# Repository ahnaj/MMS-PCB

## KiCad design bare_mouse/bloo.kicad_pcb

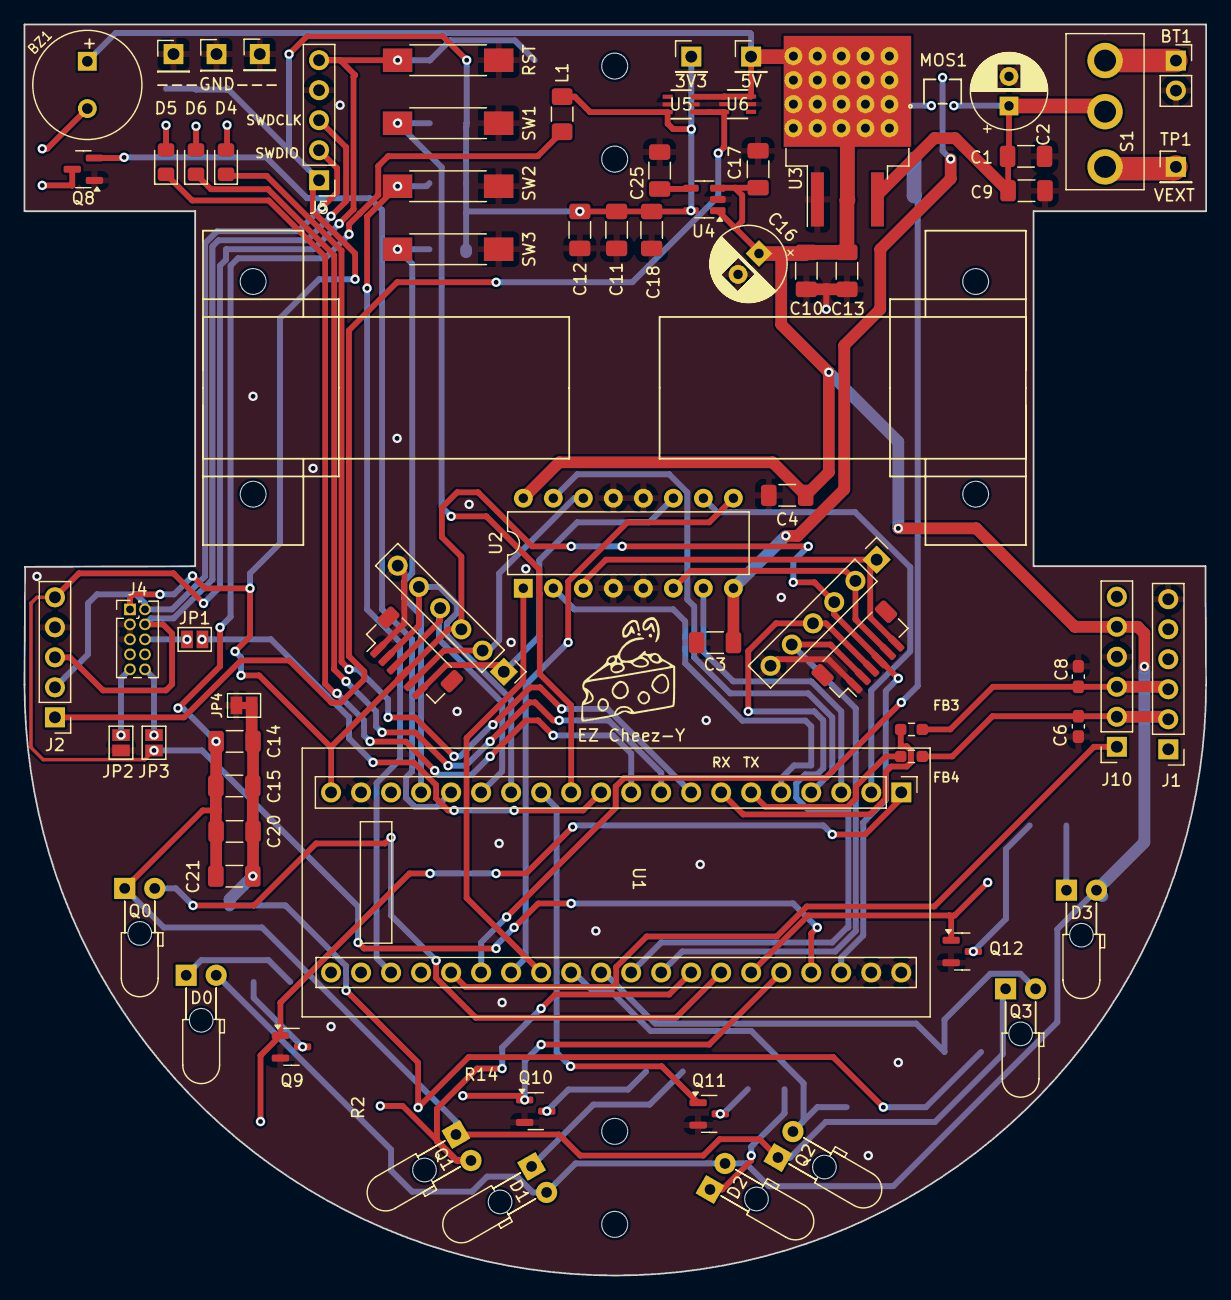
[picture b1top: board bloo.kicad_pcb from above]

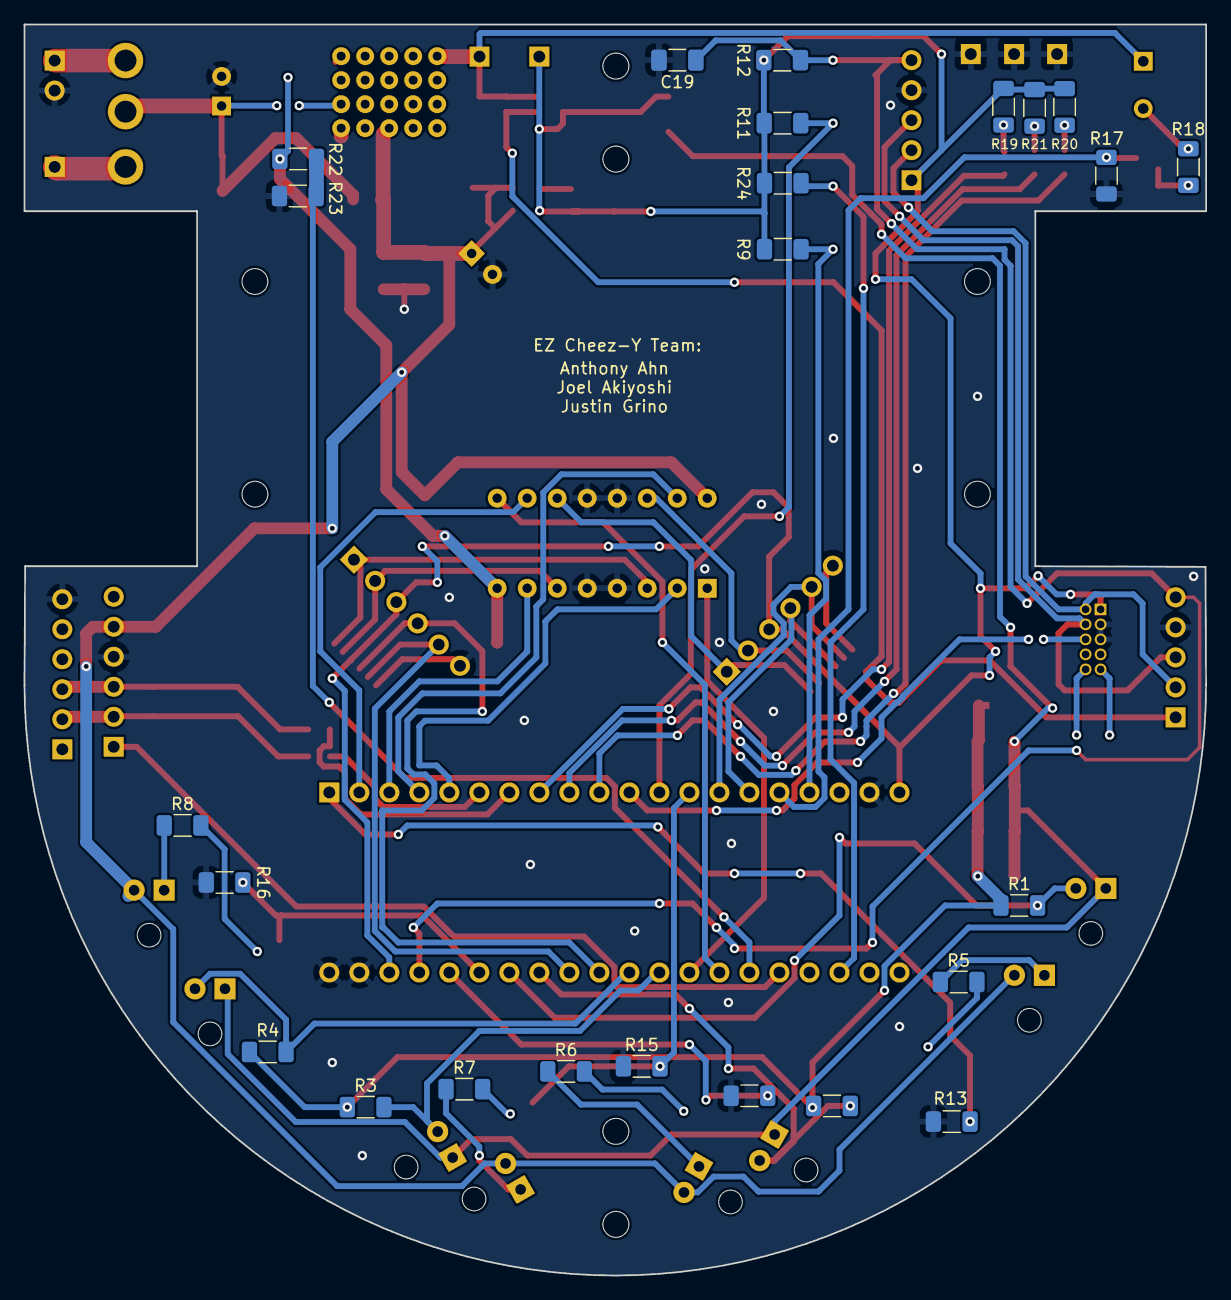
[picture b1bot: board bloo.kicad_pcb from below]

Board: 2 copper layers, 100.0 x 105.9 mm, 99 parts (24 on the bottom side), 66 nets.

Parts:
BT1: Battery_Cell; PinSocket_1x02_P2.54mm_Vertical
BZ1: Buzzer; MagneticBuzzer_PUI_AT-0927-TT-6-R
C1, C4, C12, C13, C19: 0.1uF; C_1206_3216Metric_Pad1.33x1.80mm_HandSolder
C2, C16: 100uF; CP_Radial_D6.3mm_P2.50mm
C3, C14, C15, C17, C18, C20, C21: 1uF; C_1206_3216Metric_Pad1.33x1.80mm_HandSolder
C6, C8: 22pF; C_0603_1608Metric_Pad1.08x0.95mm_HandSolder
C9, C11: 10uF; C_1206_3216Metric_Pad1.33x1.80mm_HandSolder
C10: 10uF(Tantalum); C_1206_3216Metric_Pad1.33x1.80mm_HandSolder
C25: 10nF; C_1206_3216Metric_Pad1.33x1.80mm_HandSolder
D0, D1, D2, D3: SFH4545; Emitter
D4, D5, D6: LED; LED_0805_2012Metric_Pad1.15x1.40mm_HandSolder
FB3, FB4: HZ0603C601R-10; R_0603_1608Metric_Pad0.98x0.95mm_HandSolder
J1: Serial Debug Header; PinHeader_1x06_P2.54mm_Vertical
J2, J5: SWD Header; PinHeader_1x05_P2.54mm_Vertical
J4: Conn_ARM_JTAG_SWD_10; PinHeader_2x05_P1.27mm_Vertical
J10: Conn_01x06_Female; PinSocket_1x06_P2.54mm_Vertical
JP1: JP_SWO; SolderJumper-2_P1.3mm_Open_Pad1.0x1.5mm
JP2: JP_GND; SolderJumper-2_P1.3mm_Open_Pad1.0x1.5mm
JP3: JP_RST; SolderJumper-2_P1.3mm_Open_Pad1.0x1.5mm
JP4: Jumper_2_Open; SolderJumper-2_P1.3mm_Bridged_Pad1.0x1.5mm
L1: 10uH; L_1206_3216Metric_Pad1.42x1.75mm_HandSolder
M1: M1_Conn_Alt; Motor Headers
M2: M2_Conn_Alt; Motor Headers
MOS1: SSM3K335R_LF; SOT-23F_TOS
M_MH1, M_MH2: M2; Motor_mouse
Q0, Q1, Q2, Q3: TEFT4300; Emitter
Q8: Q_NMOS_SGD; SOT-23
Q9, Q10, Q11, Q12: Q_NMOS_GSD; SOT-23
R1, R2, R3, R4: 1.8k; R_1206_3216Metric_Pad1.30x1.75mm_HandSolder
R5, R6, R7, R8: 35; R_1206_3216Metric_Pad1.30x1.75mm_HandSolder
R9, R11, R12, R24: 47K; R_1206_3216Metric_Pad1.30x1.75mm_HandSolder
R13, R14, R15, R16, R17: 47k; R_1206_3216Metric_Pad1.30x1.75mm_HandSolder
R18: 0; R_1206_3216Metric_Pad1.30x1.75mm_HandSolder
R19: 750; R_1206_3216Metric_Pad1.30x1.75mm_HandSolder
R20, R21: 75; R_1206_3216Metric_Pad1.30x1.75mm_HandSolder
R22: 20K; R_1206_3216Metric_Pad1.30x1.75mm_HandSolder
R23: 10K; R_1206_3216Metric_Pad1.30x1.75mm_HandSolder
RST: SW; SW_SPST_REED_CT05-XXXX-G1
S1: EG1218; MM Switch
SK1, SK2, SK3, SK4: M2; MountingHole_2.2mm_M2
SW1, SW2, SW3: SW; SW_SPST_REED_CT05-XXXX-G1
TP1: V_EXT_TP; PinHeader_1x01_P2.54mm_Vertical
TP2, TP5, TP6: GND_TP; PinHeader_1x01_P2.54mm_Vertical
TP3: TP_5V; PinHeader_1x01_P2.54mm_Vertical
TP4: TP_3V3; PinHeader_1x01_P2.54mm_Vertical
U1: YAAJ_BluePill_SWD_Breakout; STM32F103
U2: L293D; DIP-16_W7.62mm
U3: LM1085-5.0; 5V Voltage Reg
U4: APE8865Y5-33-HF-3; SOT-23-5
U5, U6: LM66100DCKR; DCK6_TEX

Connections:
3V3_BYP: C25.1, U4.4 (BYP)
+3.3VA: C14.1, C15.1, C20.1, C21.1, L1.2, Q0.1 (C), Q1.1 (C), Q2.1 (C), Q3.1 (C)
+3V3: C11.1, C12.1, C18.1, J4.1 (VTref), J5.1, L1.1, M1.3, M2.3, R9.1, R11.1, R12.1, R19.2, R20.2, R21.2, R24.1, TP4.1, U1.20 (3V3), U1.38 (3V3), U4.5 (VOUT), U5.6 (VOUT)
+3V3_NET: J2.1, U5.1 (VIN), U6.3 (*CE)
+5V_NET: BZ1.1 (-), C4.1, C10.1, C13.1, C16.1, C17.1, D0.2 (A), D1.2 (A), D2.2 (A), D3.2 (A), J10.5, MOS1.1, TP3.1, U2.16 (VCC1), U3.2 (VO), U4.1 (VIN), U4.3 (~SHDN), U5.3 (*CE), U6.1 (VIN), U6.6 (VOUT)
AGND: C14.2, C15.2, C20.2, C21.2, JP4.2 (B), R1.1, R2.1, R3.1, R4.1
BATT_NET: C1.2, C2.1, C9.1, MOS1.2, S1.2, U3.3 (VI)
BLE_STATE: J10.1, U1.25 (PA0)
BUTTON: R11.2, SW1.1, U1.12 (PB4)
BUTTON_2: R24.2, SW2.1, U1.23 (PC14)
BUTTON_3: R9.2, SW3.1, U1.17 (PB9)
BUZZER: Q8.2 (G), R17.2, U1.16 (PB8)
EMIT_1: Q9.1 (G), R13.2, U1.1 (PB12)
EMIT_2: Q10.1 (G), R14.2, U1.36 (PB11)
EMIT_3: Q12.1 (G), R16.2, U1.35 (PB10)
EMIT_4: Q11.1 (G), R15.2, U1.13 (PB5)
GND: BT1.2 (-), C1.1, C2.2, C3.2, C4.2, C6.2, C8.2, C9.2, C10.2, C11.2, C12.2, C13.2, C16.2, C17.2, C18.2, C19.2, C25.2, J1.6, J2.4, J4.3 (GND), J4.5 (GND), J5.4, J10.4, JP2.1 (A), JP4.1 (A), M1.6, M2.6, Q8.1 (S), Q9.2 (S), Q10.2 (S), Q11.2 (S), Q12.2 (S), R13.1, R14.1, R15.1, R16.1, R17.1, R23.2, RST.2, SW1.2, SW2.2, SW3.2, TP2.1, TP5.1, TP6.1, U1.19 (GND), U1.39 (GND), U1.40 (GND), U2.4 (GND), U2.5 (GND), U2.12 (GND), U2.13 (GND), U3.1 (GND), U4.2 (GND), U5.2 (GND), U5.5 (ST), U6.2 (GND), U6.5 (ST)
LED_BLUE: D6.1 (K), U1.9 (PA12)
LED_GREEN: D5.1 (K), U1.10 (PA15)
LED_RED: D4.1 (K), U1.8 (PA11)
M1_BACK: U1.3 (PB14), U2.7 (2A)
M1_ENC_A: M2.4, U1.31 (PA6)
M1_ENC_B: M2.5, U1.32 (PA7)
M1_FWD: U1.5 (PA8), U2.2 (1A)
M1_OUT_1: M2.1, U2.3 (1Y)
M1_OUT_2: M2.2, U2.6 (2Y)
M1_SPD: U1.28 (PA3), U2.1 (EN1,2)
M2_BACK: U1.4 (PB15), U2.15 (4A)
M2_ENC_A: M1.4, U1.15 (PB7)
M2_ENC_B: M1.5, U1.14 (PB6)
M2_FWD: U1.2 (PB13), U2.10 (3A)
M2_OUT_1: M1.1, U2.11 (3Y)
M2_OUT_2: M1.2, U2.14 (4Y)
M2_SPD: U1.27 (PA2), U2.9 (EN3,4)
unnamed: BT1.1 (+), S1.1
unnamed: BZ1.2 (+), R18.2
unnamed: D0.1 (K), R5.1
unnamed: D1.1 (K), R6.1
unnamed: D2.1 (K), R7.1
unnamed: D3.1 (K), R8.1
unnamed: D4.2 (A), R19.1
unnamed: D5.2 (A), R20.1
unnamed: D6.2 (A), R21.1
unnamed: C6.1, FB4.1, J1.2, J10.2
unnamed: C8.1, FB3.2, J1.3, J10.3
unnamed: J4.9 (GNDDetect), JP2.2 (B)
unnamed: J4.6 (SWO/TDO), JP1.1 (A)
unnamed: J4.10 (~RESET), JP3.2 (B)
unnamed: Q8.3 (D), R18.1
unnamed: Q9.3 (D), R5.2
unnamed: Q10.3 (D), R6.2
unnamed: Q11.3 (D), R7.2
unnamed: Q12.3 (D), R8.2
unnamed: S1.3, TP1.1
RECEIV_1: Q0.2 (E), R1.2, U1.34 (PB1)
RECEIV_2: Q1.2 (E), R2.2, U1.33 (PB0)
RECEIV_3: Q3.2 (E), R4.2, U1.30 (PA5)
RECEIV_4: Q2.2 (E), R3.2, U1.29 (PA4)
RST: C19.1, J2.5, J5.5, JP3.1 (A), R12.2, RST.1, U1.37 (RST)
SWDCLK: J2.3, J4.4 (SWDCLK/TCK), J5.3
SWDIO: J2.2, J4.2 (SWDIO/TMS), J5.2
SWO: JP1.2 (B), U1.11 (PB3)
USART1_RX: FB3.1, U1.7 (PA10)
USART1_TX: FB4.2, U1.6 (PA9)
VCC: C3.1, MOS1.3, R22.1, U2.8 (VCC2)
V_METER: R22.2, R23.1, U1.26 (PA1)

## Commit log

2024-11-26 updating repo with Justin's pcb
2024-11-26 placed components and attempted power traces
2024-12-06 check in modifications
2024-12-06 Resistors traces (#2)
    * placed components and attempted power traces
    * check in modifications
    ---------
2024-12-06 moved capacitors to back
2024-12-06 mira's revisions
2024-12-06 Routing (#3)
    * moved capacitors to back
    * mira's revisions
2024-12-06 Tried starting to route again
2024-12-13 no drc errors for components u4 and u5
2024-12-17 power module
2024-12-19 Finished traces for power modules, around 75% complete, need to efficiently work on motor drivers to connect them to the STM32 without chaos
2024-12-20 Finished routing, DRC shows 8 errors having to do with SWD header module
2024-12-20 Finished routing the mouse, referenced design notes to finalize silkscreen, rearranged SWD header module to fix previous errors - current final draft of the rat
2025-01-02 Fixed minor typo on back silkscreen
